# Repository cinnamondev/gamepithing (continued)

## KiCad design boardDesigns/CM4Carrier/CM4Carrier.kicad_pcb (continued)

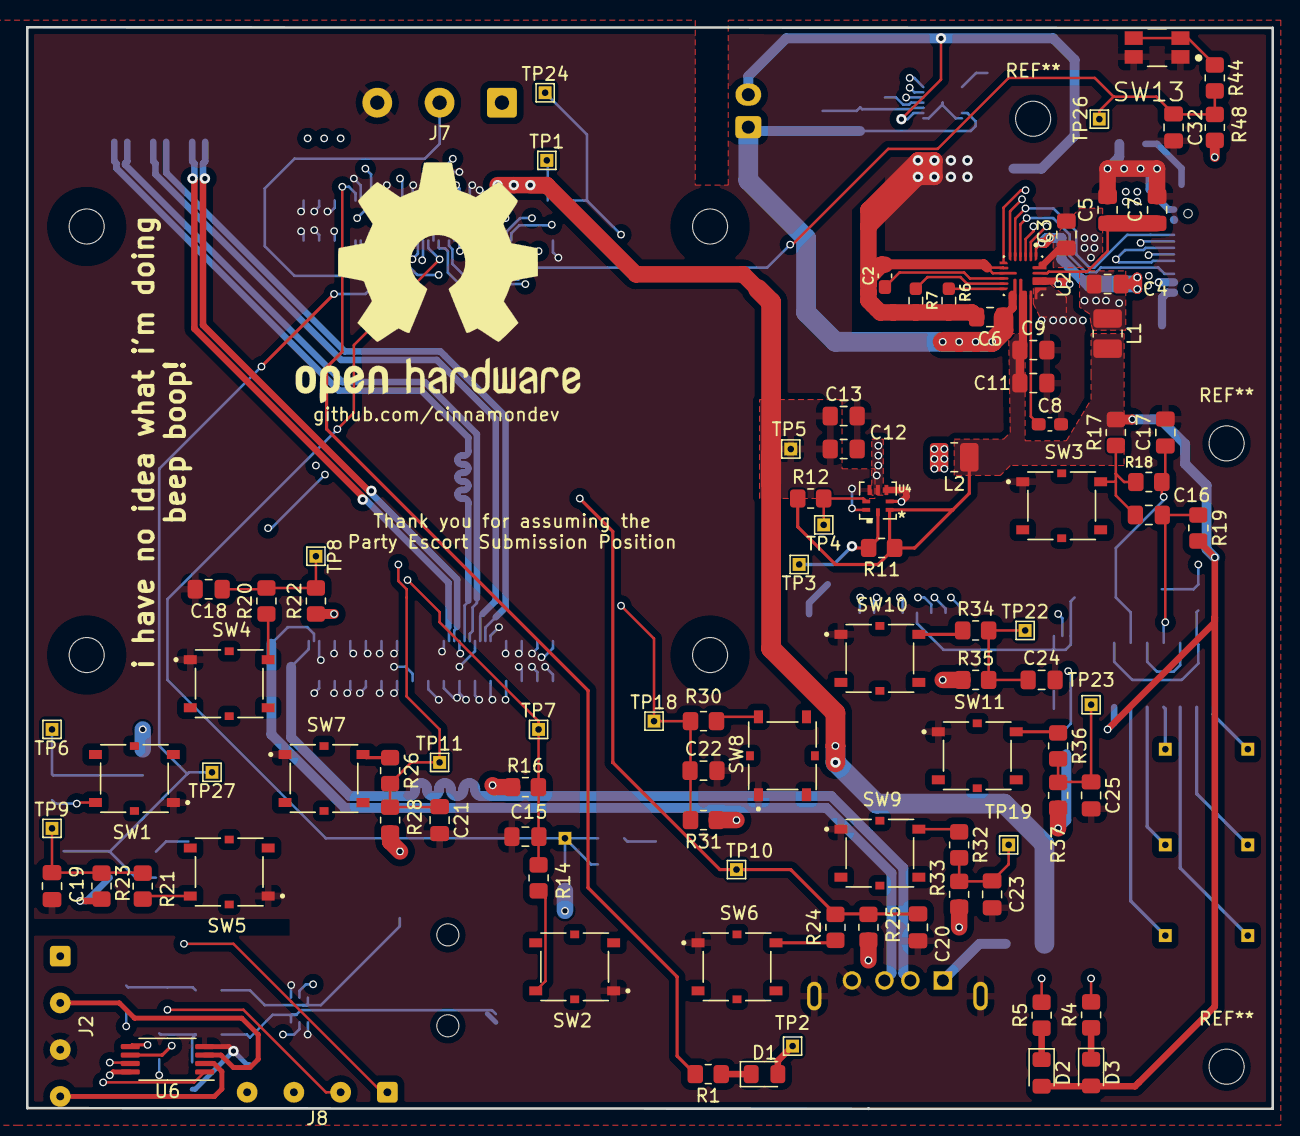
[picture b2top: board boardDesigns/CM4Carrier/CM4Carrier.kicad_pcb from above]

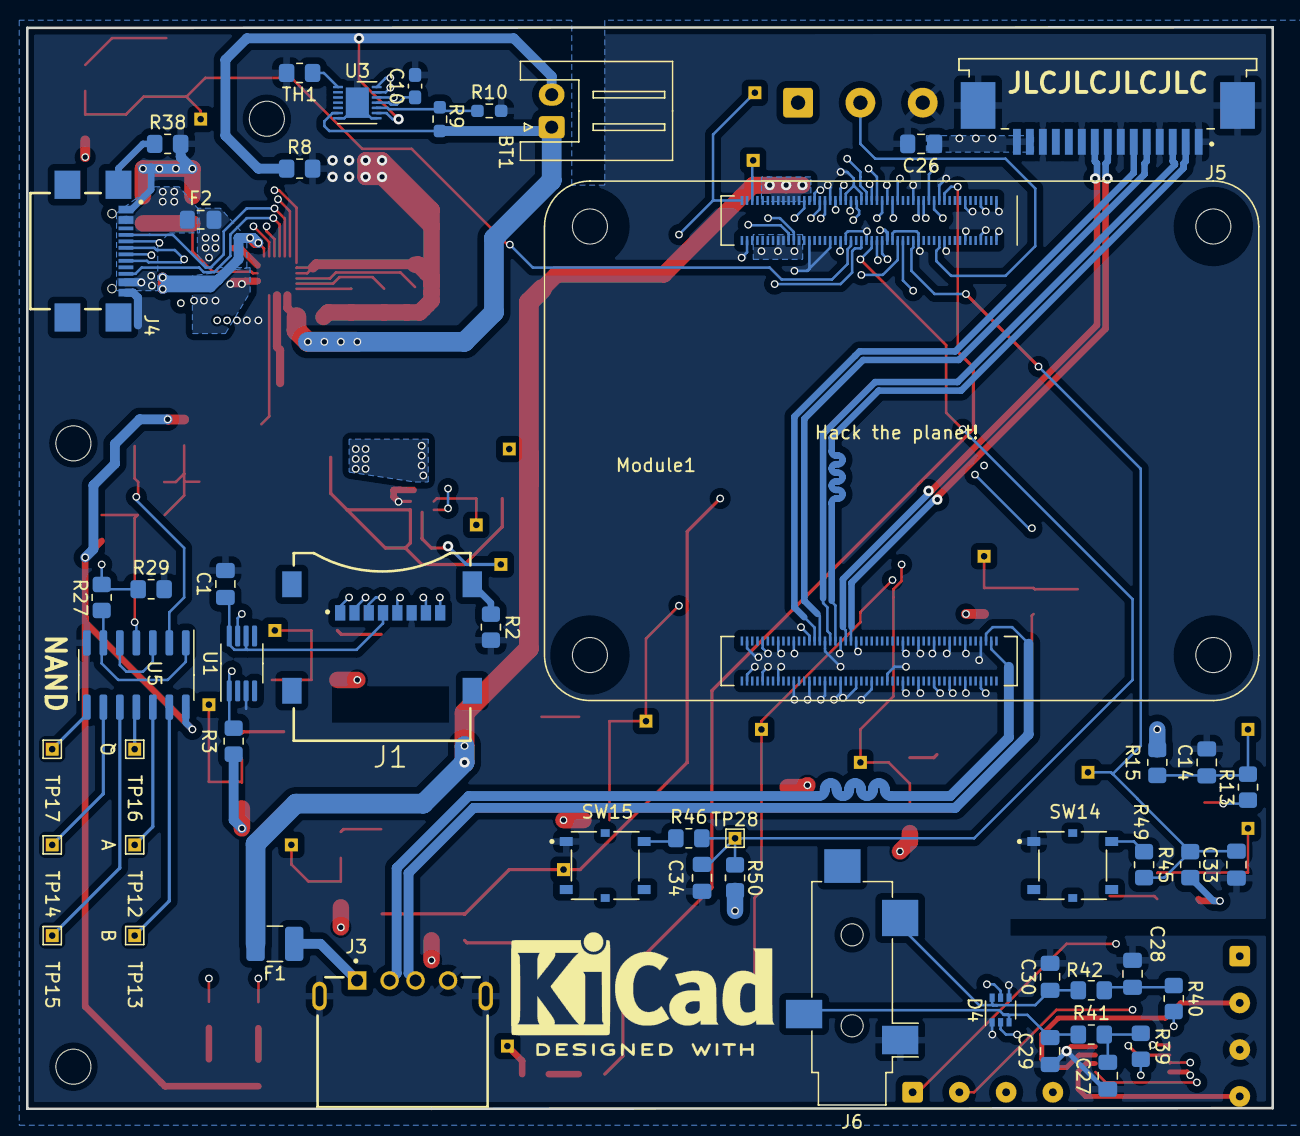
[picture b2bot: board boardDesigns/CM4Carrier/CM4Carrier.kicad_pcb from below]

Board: 4 copper layers, 95.9 x 83.3 mm, 145 parts (51 on the bottom side), 105 nets.

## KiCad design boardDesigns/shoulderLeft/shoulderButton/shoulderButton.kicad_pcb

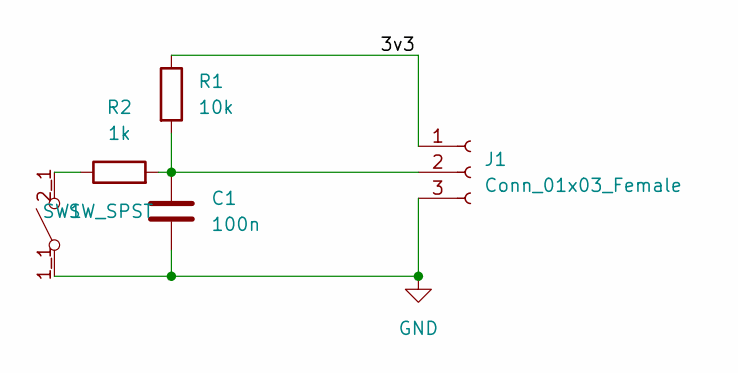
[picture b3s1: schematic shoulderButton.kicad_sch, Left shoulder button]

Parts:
C1: 100n; C_0805_2012Metric_Pad1.18x1.45mm_HandSolder
J1: Conn_01x03_Female; SolderWire-0.1sqmm_1x03_P3.6mm_D0.4mm_OD1mm
R1: 10k; R_0805_2012Metric_Pad1.20x1.40mm_HandSolder
R2: 1k; R_0805_2012Metric_Pad1.20x1.40mm_HandSolder
SW1: SW_SPST; SW_EVQ-P7J01P

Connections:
/3v3: J1.1, R1.1
GND: C1.2, J1.3, SW1.1_1 (A), SW1.1_2 (A)
unnamed: C1.1, J1.2, R1.2, R2.2
unnamed: R2.1, SW1.2_1 (B), SW1.2_2 (B)

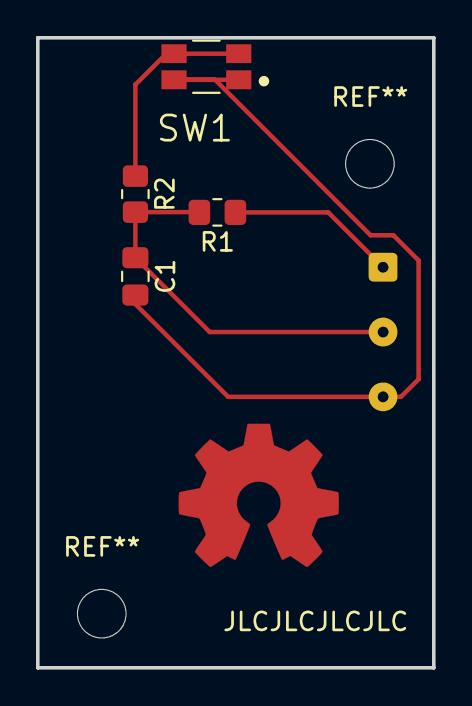
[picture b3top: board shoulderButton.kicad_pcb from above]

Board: 2 copper layers, 22.0 x 35.0 mm, 5 parts (1 on the bottom side), 4 nets.

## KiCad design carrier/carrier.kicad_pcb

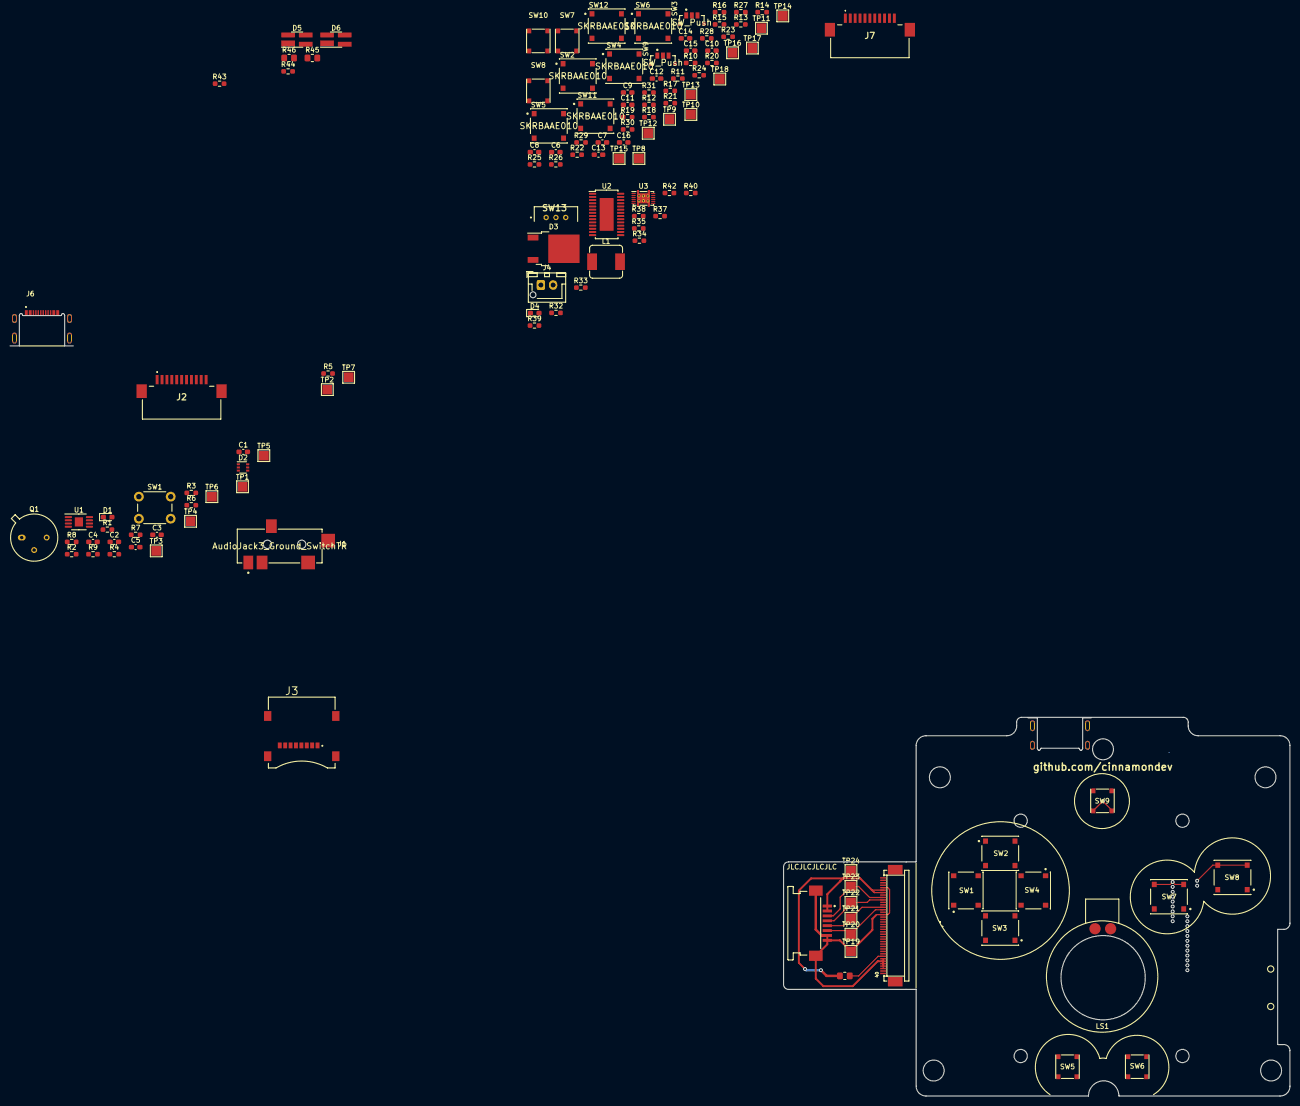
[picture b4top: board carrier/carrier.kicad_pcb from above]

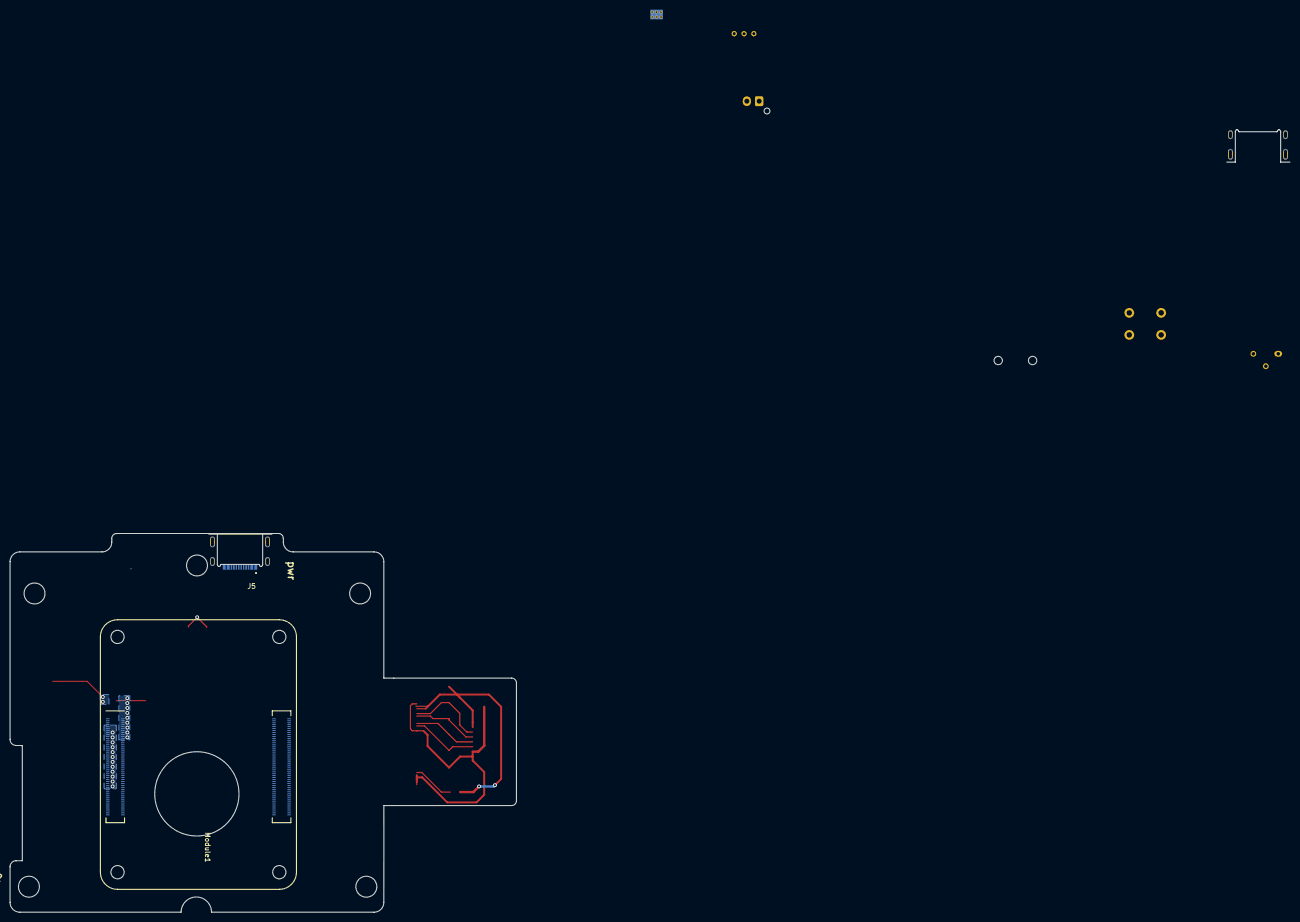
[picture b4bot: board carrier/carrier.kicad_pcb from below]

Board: 4 copper layers, 129 parts (2 on the bottom side), 87 nets.

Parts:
C1, C3: 33n; C_0603_1608Metric_Pad1.08x0.95mm_HandSolder
C2, C4: 10u; C_0603_1608Metric_Pad1.08x0.95mm_HandSolder
C5: 10uF; C_0603_1608Metric_Pad1.08x0.95mm_HandSolder
C6, C7, C8, C9, C10, C11, C12, C13, C14, C15, C16: 100n; C_0603_1608Metric_Pad1.08x0.95mm_HandSolder
D1: LED; LED_0603_1608Metric_Pad1.05x0.95mm_HandSolder
D2: BAV99S; SOT-363_SC-70-6
D3: D_Schottky; TO-252-2
D4: PG; LED_0603_1608Metric_Pad1.05x0.95mm_HandSolder
D5: 8240119; SOT-143R_Reverse_Handsoldering
D6: 8240116; SOT-143R_Reverse_Handsoldering
J1: AudioJack3_Ground_SwitchTR; CUI-SJ-43515TS-SMT-TR-0
J2, J7: Conn_01x10; 522711169
J3: Micro_SD_Card; GCT_MEM2067-02-180-00-A_REVB
J4: JST BATTERY CONN.; JST_XH_B2B-XH-AM_1x02_P2.50mm_Vertical
J5, J6#2: USB_C_Receptacle_USB2.0; GCT_USB4510-03-1-A_REVA
J6: 52271-0879; Molex-52271-0879-Manufacturer_Recommended
L1: 1uH; L_Sumida_CDMC6D28_7.25x6.5mm
LS1: Speaker; speaker
Module1: ComputeModule4-CM4; Raspberry-Pi-4-Compute-Module
Q1: 2N2219; TO-39-3
R1, R37: 220; R_0603_1608Metric_Pad0.98x0.95mm_HandSolder
R2, R34: 1M; R_0603_1608Metric_Pad0.98x0.95mm_HandSolder
R3, R5: 270; R_0603_1608Metric_Pad0.98x0.95mm_HandSolder
R4, R6: 150; R_0603_1608Metric_Pad0.98x0.95mm_HandSolder
R7: 15k; R_0603_1608Metric_Pad0.98x0.95mm_HandSolder
R8: 12k 1%; R_0603_1608Metric_Pad0.98x0.95mm_HandSolder
R9: 0; R_0603_1608Metric_Pad0.98x0.95mm_HandSolder
R10, R12, R14, R15, R18, R20, R22, R24, R26, R28, R30: 1k; R_0603_1608Metric_Pad0.98x0.95mm_HandSolder
R11, R13, R16, R17, R19, R21, R23, R25, R27, R29, R31, R39: 10k; R_0603_1608Metric_Pad0.98x0.95mm_HandSolder
R32: nc; R_0603_1608Metric_Pad0.98x0.95mm_HandSolder
R33: 540k; R_0603_1608Metric_Pad0.98x0.95mm_HandSolder
R35: 270k; R_0603_1608Metric_Pad0.98x0.95mm_HandSolder
R38, R40, R42, R43, R44: 5.1k; R_0603_1608Metric_Pad0.98x0.95mm_HandSolder
R45, R46: 56k; R_0805_2012Metric_Pad1.20x1.40mm_HandSolder
R47: 33; R_0805_2012Metric_Pad1.20x1.40mm_HandSolder
SW1, SW2, SW3#2, SW4, SW7, SW8#2: SKRRACE010; ALPS-SKRRACE010-0-0-MFG
SW1#2: SW_Push; SW_PUSH_6mm_H4.3mm
SW2#2, SW4#2, SW5, SW6, SW11, SW12: SKRBAAE010; ALPS-SKRRACE010-0-0-MFG
SW3, SW9: SW_Push; Panasonic-EVP-AEJB2A-MFG
SW5#2, SW6#2, SW9#2: SKRBAAE010
SW7#2, SW8, SW10: SKRRACE010; SKRBAAE010
SW13: SW_SPDT; SS3HVB
TP1: GLOBALEN; TestPoint_Pad_2.0x2.0mm
TP2, TP19: GND; TestPoint_Pad_2.0x2.0mm
TP3, TP20: MOSI; TestPoint_Pad_2.0x2.0mm
TP4, TP21: MISO; TestPoint_Pad_2.0x2.0mm
TP5, TP22: SCLK; TestPoint_Pad_2.0x2.0mm
TP6, TP23: CEO_N; TestPoint_Pad_2.0x2.0mm
TP7, TP24: +3.3V; TestPoint_Pad_2.0x2.0mm
TP8: LEFT; TestPoint_Pad_2.0x2.0mm
TP9: L; TestPoint_Pad_2.0x2.0mm
TP10: UP; TestPoint_Pad_2.0x2.0mm
TP11: DOWN; TestPoint_Pad_2.0x2.0mm
TP12: RIGHT; TestPoint_Pad_2.0x2.0mm
TP13: R; TestPoint_Pad_2.0x2.0mm
TP14: BKL; TestPoint_Pad_2.0x2.0mm
TP15: SEL; TestPoint_Pad_2.0x2.0mm
TP16: STR; TestPoint_Pad_2.0x2.0mm
TP17: B; TestPoint_Pad_2.0x2.0mm
TP18: A; TestPoint_Pad_2.0x2.0mm
U1: AP22814AW5; MSOP-8-1EP_3x3mm_P0.65mm_EP1.68x1.88mm
U2: MAX1709; TSSOP-28-1EP_4.4x9.7mm_P0.65mm_EP2.85x6.7mm
U3: BQ27441DRZT-G1B; Texas_S-PDSO-N12
U4: ER-CON40HT-1

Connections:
/+3.3v: D1.2 (A), D2.2 (K2), D2.5 (K4), J2.8, J2.9, J2.10, Module1.78 (GPIO_VREF(1.8v/3.3v_Input)), Module1.84 (+3.3v_(Output)), R8.1, R11.1, R13.1, R16.1, R17.1, R19.1, R21.1, R23.1, R25.1, R27.1, R29.1, R31.1, TP7.1, U1.2 (IN)
/+5v: D3.1 (K), D4.2 (A), D6.4 (VDD), LS1.1, Module1.77 (+5v_(Input)), R7.1, R35.1, R45.1, R46.1
/Battery Charger/+3.3v: R38.1, R40.1, R42.1
/Battery Charger/BAT+: J4.2, U3.6 (BAT), U3.7 (SRN)
/Battery Charger/GPOUT: R38.2, U3.12 (GPOUT)
/Battery Charger/POWERSWITCH: R33.2, R35.2, SW13.B1 (C)
/Battery Charger/SCL: R42.2, U3.2 (SCL)
/Battery Charger/SDA: R40.2, U3.1 (SDA)
/Battery Charger/VG3H: L1.2, U3.8 (SRP)
/Buttons/BTN_A: C16.1, Module1.41 (GPIO25), R30.2, R31.2, TP18.1
/Buttons/BTN_B: C15.1, Module1.29 (GPIO16), R28.2, R29.2, TP17.1
/Buttons/BTN_BACKLIGHT: C12.1, Module1.27 (GPIO20), R22.2, R23.2
/Buttons/BTN_SELECT: C11.1, Module1.45 (GPIO24), R20.2, R21.2
/Buttons/BTN_START: C14.1, Module1.25 (GPIO21), R26.2, R27.2
/Buttons/DPAD_DOWN: C9.1, Module1.34 (GPIO5), R15.2, R17.2, TP11.1
/Buttons/DPAD_LEFT: C6.1, Module1.24 (GPIO26), R10.2, R11.2, TP8.1
/Buttons/DPAD_RIGHT: C10.1, Module1.31 (GPIO12), R18.2, R19.2
/Buttons/DPAD_UP: C8.1, Module1.50 (GPIO17), R14.2, R16.2, TP10.1
/Buttons/SHOULDER_L: C7.1, Module1.46 (GPIO22), R12.2, R13.2, TP9.1
/Buttons/SHOULDER_R: C13.1, Module1.47 (GPIO23), R24.2, R25.2, TP13.1
/CM4/AUX0: Module1.49 (GPIO18), R5.1
/CM4/AUX1: Module1.26 (GPIO19), R3.1
/CM4/GLOBAL_EN: Module1.99 (Global_EN), SW1#2.1, TP1.1
/CM4/SCREEN_CE0_N: J2.7, Module1.39 (GPIO8), TP6.1
/CM4/SCREEN_MISO: J2.5, Module1.40 (GPIO9), TP4.1
/CM4/SCREEN_MOSI: J2.4, Module1.44 (GPIO10), TP3.1
/CM4/SCREEN_SCLK: J2.6, Module1.38 (GPIO11), TP5.1
/CM4/SD_CLK: J3.5 (CLK), Module1.57 (SD_CLK)
/CM4/SD_CMD: J3.3 (CMD), Module1.62 (SD_CMD)
/CM4/SD_DAT0: J3.7 (DAT0), Module1.63 (SD_DAT0)
/CM4/SD_DAT1: J3.8 (DAT1), Module1.67 (SD_DAT1)
/CM4/SD_DAT2: J3.1 (DAT2), Module1.69 (SD_DAT2)
/CM4/SD_DAT3: J3.2 (DAT3/CD), Module1.61 (SD_DAT3)
/CM4/SD_PWR: C5.1, J3.4 (VDD)
/CM4/SD_PWR_ON: Module1.75 (SD_PWR_ON), R8.2, U1.4 (EN)
/Connectors/USB2_D+: D6.2 (I/O1), J5.A6 (D+), J5.B6 (D+), Module1.105 (USB2_P)
/Connectors/USB2_D-: D6.3 (I/O2), J5.A7 (D-), J5.B7 (D-), Module1.103 (USB2_N)
/Display board (SNAP OFF BOARD)/+3.3v: J6.1, J6.2, J7.8, J7.9, J7.10, R47.1, TP24.1, U4.6 (IOVCC), U4.7 (VCI), U4.39 (IM1), U4.40 (IM2)
/Display board (SNAP OFF BOARD)/SPI0_CE0_N: J6.3, J7.7, TP23.1, U4.9 (CS/SPI_CS)
/Display board (SNAP OFF BOARD)/SPI0_MOSI: J6.6, J7.4, TP20.1, U4.14 (SDO_SPI)
/Display board (SNAP OFF BOARD)/SPI0_SCLK: J6.4, J7.6, TP22.1, U4.10 (DC/SCL_SPI)
/Display board (SNAP OFF BOARD)/SPI_MISO: J6.5, J7.5, TP21.1, U4.13 (SDI_SPI_SDA)
GND: C1.1, C3.1, C5.2, C6.2, C7.2, C8.2, C9.2, C10.2, C13.2, C15.2, C16.2, D2.1 (A1), D2.4 (A3), D5.1 (GND), D6.1 (GND), J2.1, J2.2, J2.3, J3.6 (VSS), J4.1, Module1.1 (GND), Module1.2 (GND), Module1.3 (Ethernet_Pair3_P), Module1.4 (Ethernet_Pair1_P), Module1.5 (Ethernet_Pair3_N), Module1.6 (Ethernet_Pair1_N), Module1.7 (GND), Module1.8 (GND), Module1.9 (Ethernet_Pair2_N), Module1.10 (Ethernet_Pair0_N), Module1.11 (Ethernet_Pair2_P), Module1.12 (Ethernet_Pair0_P), Module1.13 (GND), Module1.14 (GND), Module1.15 (Ethernet_nLED3(3.3v)), Module1.16 (Ethernet_SYNC_IN(1.8v)), Module1.17 (Ethernet_nLED2(3.3v)), Module1.18 (Ethernet_SYNC_OUT(1.8v)), Module1.19 (Ethernet_nLED1(3.3v)), Module1.20 (EEPROM_nWP), Module1.22 (GND), Module1.23 (GND), Module1.32 (GND), Module1.33 (GND), Module1.42 (GND), Module1.43 (GND), Module1.52 (GND), Module1.53 (GND), Module1.59 (GND), Module1.60 (GND), Module1.65 (GND), Module1.66 (GND), Module1.71 (GND), Module1.74 (GND), Module1.98 (GND), Module1.101 (USB_OTG_ID), Module1.102 (PCIe_CLK_nREQ), Module1.107 (GND), Module1.108 (GND), Module1.110 (PCIe_CLK_P), Module1.112 (PCIe_CLK_N), Module1.113 (GND), Module1.114 (GND), Module1.116 (PCIe_RX_P), Module1.118 (PCIe_RX_N), Module1.119 (GND), Module1.120 (GND), Module1.122 (PCIe_TX_P), Module1.124 (PCIe_TX_N), Module1.125 (GND), Module1.126 (GND), Module1.128 (CAM0_D0_N), Module1.130 (CAM0_D0_P), Module1.131 (GND), Module1.132 (GND), Module1.134 (CAM0_D1_N), Module1.136 (CAM0_D1_P), Module1.137 (GND), Module1.138 (GND), Module1.140 (CAM0_C_N), Module1.142 (CAM0_C_P), Module1.144 (GND), Module1.146 (HDMI1_TX2_P), Module1.147 (HDMI1_SCL), Module1.148 (HDMI1_TX2_N), Module1.150 (GND), Module1.152 (HDMI1_TX1_P), Module1.154 (HDMI1_TX1_N), Module1.155 (GND), Module1.156 (GND), Module1.157 (DSI0_D0_N), Module1.158 (HDMI1_TX0_P), Module1.159 (DSI0_D0_P), Module1.160 (HDMI1_TX0_N), Module1.161 (GND), Module1.162 (GND), Module1.163 (DSI0_D1_N), Module1.164 (HDMI1_CLK_P), Module1.165 (DSI0_D1_P), Module1.166 (HDMI1_CLK_N), Module1.167 (GND), Module1.168 (GND), Module1.169 (DSI0_C_N), Module1.171 (DSI0_C_P), Module1.173 (GND), Module1.174 (GND), Module1.175 (DSI1_D0_N), Module1.177 (DSI1_D0_P), Module1.179 (GND), Module1.180 (GND), Module1.181 (DSI1_D1_N), Module1.183 (DSI1_D1_P), Module1.185 (GND), Module1.186 (GND), Module1.187 (DSI1_C_N), Module1.189 (DSI1_C_P), Module1.191 (GND), Module1.192 (GND), Module1.193 (DSI1_D2_N), Module1.194 (DSI1_D3_N), Module1.195 (DSI1_D2_P), Module1.196 (DSI1_D3_P), Module1.197 (GND), Module1.198 (GND), Q1.1 (E), R2.2, R4.1, R6.2, R9.1, R32.2, R33.1, R34.1, R37.2, R39.2, R43.2, R44.2, SW1.2, SW1.4, SW2.2, SW2.4, SW2#2.2, SW2#2.4, SW3.1, SW3#2.2, SW3#2.4, SW4.2, SW4.4, SW4#2.2, SW4#2.4, SW5.2, SW5.4, SW5#2.2, SW5#2.4, SW6.2, SW6.4, SW6#2.2, SW6#2.4, SW7.2, SW7.4, SW7#2.2, SW8.2, SW8#2.2, SW8#2.4, SW9.1, SW9#2.2, SW9#2.4, SW10.2, SW11.2, SW11.4, SW12.2, SW12.4, SW13.C1 (B), TP2.1, U1.1 (GND), U3.3 (VSS), U3.13 (PAD)
GND1: J6.7, J6.8, J6.MP1, J6.MP2, U4.5 (GND), U4.16 (GND), U4.34 (LEDK), U4.35 (LEDK), U4.36 (LEDK), U4.37 (GND), U4.38 (IMO)
unnamed: C1.2, C2.1, R3.2, R4.2
unnamed: C2.2, D2.6 (K3A4)
unnamed: C3.2, C4.1, R5.2, R6.1
unnamed: C4.2, D2.3 (K1A2)
unnamed: C11.2, SW7#2.4
unnamed: C12.2, SW8.4
unnamed: C14.2, SW10.4
unnamed: D1.1 (K), R1.2
unnamed: D3.2 (A), L1.1
unnamed: D4.1 (K), R37.1
unnamed: D5.2 (I/O1), J6#2.A6 (D+), J6#2.B6 (D+)
unnamed: D5.3 (I/O2), J6#2.A7 (D-), J6#2.B7 (D-)
unnamed: Q1.2 (B), R7.2
unnamed: J3.9 (SHIELD), R9.2
unnamed: J5.A5 (CC1), R46.2
unnamed: J5.B5 (CC2), R45.2
unnamed: J6#2.A5 (CC1), R44.1
unnamed: J6#2.B5 (CC2), R43.1
unnamed: J7.1, J7.2, J7.3, TP19.1
unnamed: LS1.2, Q1.3 (C)
unnamed: Module1.21 (PI_nLED_Activity), R1.1
unnamed: Module1.85 (+5v_(Input)), Module1.87 (+5v_(Input))
unnamed: SW1.1, SW1.3
unnamed: R2.1, SW1#2.2
unnamed: SW2.1, SW2.3
unnamed: SW3#2.1, SW3#2.3
unnamed: SW4.1, SW4.3
unnamed: SW8#2.1, SW8#2.3
unnamed: R10.1, SW2#2.1, SW2#2.3
unnamed: SW7.1, SW7.3
unnamed: R12.1, SW3.2
unnamed: R14.1, SW4#2.1, SW4#2.3
unnamed: R15.1, SW5.1, SW5.3
unnamed: R18.1, SW6.1, SW6.3
unnamed: R20.1, SW7#2.3
unnamed: R22.1, SW8.3
unnamed: R24.1, SW9.2
unnamed: R26.1, SW5#2.1, SW5#2.3, SW10.3
unnamed: R28.1, SW9#2.1, SW9#2.3, SW11.1, SW11.3
unnamed: R30.1, SW12.1, SW12.3
unnamed: SW6#2.1, SW6#2.3
unnamed: R39.1, U3.10 (BIN)
unnamed: R47.2, U4.33 (LEDA)

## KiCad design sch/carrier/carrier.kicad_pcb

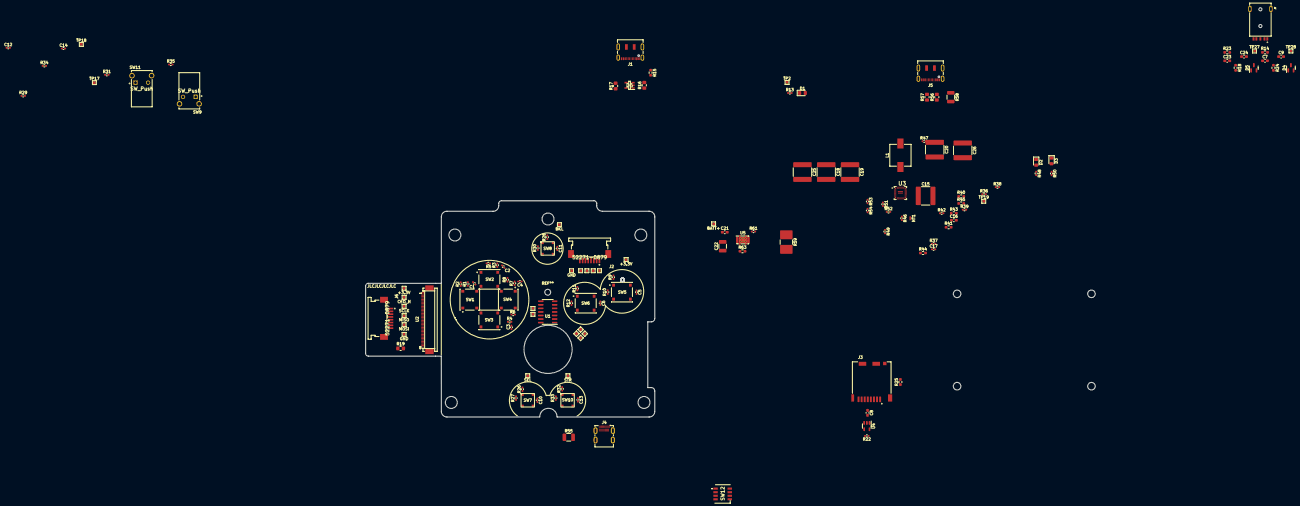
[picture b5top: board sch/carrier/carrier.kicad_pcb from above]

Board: 2 copper layers, 103.3 x 77.2 mm, 146 parts (1 on the bottom side), 110 nets, no tracks yet.

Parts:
C1, C2, C3, C4, C5, C6, C10, C11, C12, C13, C14: 0.1uF; C_0402_1005Metric_Pad0.74x0.62mm_HandSolder
C7, C23: 33n; C_0603_1608Metric_Pad1.08x0.95mm_HandSolder
C8: 10uF; C_0603_1608Metric_Pad1.08x0.95mm_HandSolder
C9, C24: 10u; C_0603_1608Metric_Pad1.08x0.95mm_HandSolder
C15: 10uF; C_2225_5664Metric_Pad1.80x6.60mm_HandSolder
C16: 100nF; C_0603_1608Metric_Pad1.08x0.95mm_HandSolder
C17: 100nf; C_0402_1005Metric_Pad0.74x0.62mm_HandSolder
C18: 22u; C_2225_5664Metric_Pad1.80x6.60mm_HandSolder
C19, C20, C25, C26: 10u; C_2225_5664Metric_Pad1.80x6.60mm_HandSolder
C21: 1uF; C_0603_1608Metric_Pad1.08x0.95mm_HandSolder
C22: 0.47uF; C_1210_3225Metric_Pad1.33x2.70mm_HandSolder
D1, D2, D3: LED; LED_0805_2012Metric_Pad1.15x1.40mm_HandSolder
D4, D5: BAV99; SOT-23
D6: 824011; SOT95P280X145-5N
J1, J5: USB_C_Receptacle_USB2.0; USB_C_Receptacle_JAE_DX07S016JA1R1500
J2, J6: 52271-0879; Molex-52271-0879-Manufacturer_Recommended
J3: Micro_SD_Card; HRS_DM3CS-SF
J4: HDMI_D_1.4; HDMI_Micro-D_Molex_46765-1x01
J7: AudioJack3_Switch; audio
L1: 6.8uH; L_Wuerth_WE-PD-Typ-M-Typ-S_Handsoldering
Module0: ComputeModule4-CM4; Raspberry-Pi-4-Compute-Module
NT1: NetTie; NetTie-2_SMD_Pad0.5mm
R1, R3, R4, R7, R9, R11, R26, R28, R29, R32, R34, R36, R39: 1k; R_0402_1005Metric_Pad0.72x0.64mm_HandSolder
R2, R5, R6, R8, R10, R12, R27, R30, R31, R33, R35, R61: 10k; R_0402_1005Metric_Pad0.72x0.64mm_HandSolder
R13: 220; R_0402_1005Metric_Pad0.72x0.64mm_HandSolder
R14, R23: 270; R_0603_1608Metric_Pad0.98x0.95mm_HandSolder
R15, R25: 0; R_0603_1608Metric_Pad0.98x0.95mm_HandSolder
R16, R17: 56k; R_0805_2012Metric_Pad1.20x1.40mm_HandSolder
R18, R24: 150; R_0603_1608Metric_Pad0.98x0.95mm_HandSolder
R19: 33; R_0805_2012Metric_Pad1.20x1.40mm_HandSolder
R22: 12k 1%; R_0402_1005Metric_Pad0.72x0.64mm_HandSolder
R37: 9k; R_0402_1005Metric_Pad0.72x0.64mm_HandSolder
R38: 1.3k; R_0402_1005Metric_Pad0.72x0.64mm_HandSolder
R40, R41: 10.5k; R_0603_1608Metric_Pad0.98x0.95mm_HandSolder
R42: 16k; R_0402_1005Metric_Pad0.72x0.64mm_HandSolder
R43, R63: 10k; R_0603_1608Metric_Pad0.98x0.95mm_HandSolder
R44: 3k; R_0603_1608Metric_Pad0.98x0.95mm_HandSolder
R45: 55.2k; R_0603_1608Metric_Pad0.98x0.95mm_HandSolder
R46: 120k; R_0402_1005Metric_Pad0.72x0.64mm_HandSolder
R47: 20m; R_0402_1005Metric_Pad0.72x0.64mm_HandSolder
R48, R49, R50: 2.49k; R_0402_1005Metric_Pad0.72x0.64mm_HandSolder
R51, R52, R53, R54: 10.5k; R_0402_1005Metric_Pad0.72x0.64mm_HandSolder
R55, R58: 0; R_1210_3225Metric_Pad1.30x2.65mm_HandSolder
R56, R57: 5.1k; R_0805_2012Metric_Pad1.20x1.40mm_HandSolder
R59: 10m; R_2816_7142Metric_Pad3.20x4.45mm_HandSolder
SW1, SW2, SW3, SW4, SW5, SW6: SKRRACE010; ALPS-SKRRACE010-0-0-MFG
SW7, SW8, SW10: SKRBAAE010
SW9, SW11: SW_Push; TE_Connectivity-1-1825027-1-0-0-Recommended_Land_Pattern_
SW12: SW_DIP_x04; CHS04TA1
TP1, TP20: GND; TestPoint_Pad_1.0x1.0mm
TP2: Activity; TestPoint_Pad_1.0x1.0mm
TP3, TP21: CEO_N; TestPoint_Pad_1.0x1.0mm
TP4, TP22: SCLK; TestPoint_Pad_1.0x1.0mm
TP5, TP23: MISO; TestPoint_Pad_1.0x1.0mm
TP6: UP; TestPoint_Pad_1.0x1.0mm
TP7: DOWN; TestPoint_Pad_1.0x1.0mm
TP8: LEFT; TestPoint_Pad_1.0x1.0mm
TP9: RIGHT; TestPoint_Pad_1.0x1.0mm
TP10: A; TestPoint_Pad_1.0x1.0mm
TP11: B; TestPoint_Pad_1.0x1.0mm
TP12, TP24: MOSI; TestPoint_Pad_1.0x1.0mm
TP13, TP25: +3.3V; TestPoint_Pad_1.0x1.0mm
TP14: BKL; TestPoint_Pad_1.0x1.0mm
TP15: SEL; TestPoint_Pad_1.0x1.0mm
TP16: STR; TestPoint_Pad_1.0x1.0mm
TP17: L; TestPoint_Pad_1.0x1.0mm
TP18: R; TestPoint_Pad_1.0x1.0mm
TP19: +5v Output; TestPoint_Pad_1.0x1.0mm
TP26: BATT+; TestPoint_Pad_1.0x1.0mm
TP27: AUXR; TestPoint_Pad_1.0x1.0mm
TP28: AUXL; TestPoint_Pad_1.0x1.0mm
U1: SN74HC14N; SO-14_3.9x8.65mm_P1.27mm
U2: ER-CON40HT-1
U3: MP2636GR-P; IC_MP2636GR-P
U4: AP22814AW5; SOT-23-5
U5: BQ27441DRZR-G1B; Texas_S-PDSO-N12

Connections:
/+3.3v: D1.2 (A), D4.2 (A), D5.2 (A), J2.1, J2.2, Module0.78 (GPIO_VREF(1.8v/3.3v_Input)), Module0.84 (+3.3v_(Output)), R2.1, R5.1, R6.1, R8.1, R10.1, R12.1, R22.1, R27.1, R30.1, R31.1, R33.1, R35.1, TP13.1, U1.14 (VCC), U4.5 (IN)
/+5v: C18.1, C19.1, C25.1, D6.5 (VDD), J1.A4 (VBUS), J1.A9 (VBUS), J1.B4 (VBUS), J1.B9 (VBUS), J4.19 (+5V), Module0.77 (+5v_(Input)), Module0.79 (+5v_(Input)), Module0.81 (+5v_(Input)), Module0.83 (+5v_(Input)), Module0.85 (+5v_(Input)), Module0.87 (+5v_(Input)), R16.1, R17.1, R43.2, R53.1, U3.3 (SYS), U3.20 (SYS), U3.29 (SYS)
/Battery Charger/BATT: C20.1, C26.1, R47.2, R59.2, U3.17 (BATT), U5.7 (SRN)
/Battery Charger/CHRG: C15.1, J5.A4 (VBUS), J5.A9 (VBUS), J5.B4 (VBUS), J5.B9 (VBUS), R36.1, R38.1, U3.4 (VIN), U3.19 (VIN), U3.30 (VIN)
/Battery Charger/_CHIP_VCC: C16.2, R40.1, R41.1, R51.1, U3.5 (VCC)
/Battery/FUEL_SCL: Module0.80 (SCL0), U5.2 (SCL)
/Battery/FUEL_SDA: Module0.82 (SDA0), U5.1 (SDA)
/Buttons/BTN_A: Module0.41 (GPIO25), TP10.1, U1.10 (5Y)
/Buttons/BTN_B: Module0.29 (GPIO16), TP11.1, U1.12 (6Y)
/Buttons/BTN_BACKLIGHT: C11.1, Module0.27 (GPIO20), R28.2, R30.2, TP14.1
/Buttons/DPAD_DOWN: Module0.55 (GPIO14), TP7.1, U1.6 (3Y)
/Buttons/DPAD_LEFT: Module0.28 (GPIO13), TP8.1, U1.8 (4Y)
/Buttons/DPAD_RIGHT: Module0.31 (GPIO12), TP9.1, U1.4 (2Y)
/Buttons/DPAD_UP: Module0.50 (GPIO17), TP6.1, U1.2 (1Y)
/Buttons/GLOBAL_EN: Module0.99 (Global_EN), SW12.1
/Buttons/SELECT: C10.1, Module0.25 (GPIO21), R26.2, R27.2, TP15.1
/Buttons/SHOULDER_L: C12.1, Module0.46 (GPIO22), R29.2, R31.2, TP17.1
/Buttons/SHOULDER_R: C14.1, Module0.47 (GPIO23), R34.2, R35.2, TP18.1
/Buttons/START: C13.1, Module0.45 (GPIO24), R32.2, R33.2, TP16.1
/Buttons/__B_A: C5.1, R9.2, R10.2, U1.11 (5A)
/Buttons/__B_B: C6.1, R11.2, R12.2, U1.13 (6A)
/Buttons/__DP_D: C3.1, R4.2, R6.2, U1.5 (3A)
/Buttons/__DP_L: C1.2, R1.2, R2.2, U1.9 (4A)
/Buttons/__DP_R: C4.1, R7.2, R8.2, U1.3 (2A)
/Buttons/__DP_U: C2.1, R3.2, R5.2, U1.1 (1A)
/CM4/AUX0: Module0.49 (GPIO18), R23.1
/CM4/AUX1: Module0.26 (GPIO19), R14.1
/CM4/SCREEN_CE0_N: J2.3, Module0.39 (GPIO8), TP3.1
/CM4/SCREEN_MISO: J2.5, Module0.40 (GPIO9), TP5.1
/CM4/SCREEN_MOSI: J2.6, Module0.44 (GPIO10), TP12.1
/CM4/SCREEN_SCLK: J2.4, Module0.38 (GPIO11), TP4.1
/CM4/SD_CLK: J3.5 (CLK), Module0.57 (SD_CLK)
/CM4/SD_CMD: J3.3 (CMD), Module0.62 (SD_CMD)
/CM4/SD_DAT0: J3.7 (DAT0), Module0.63 (SD_DAT0)
/CM4/SD_DAT1: J3.8 (DAT1), Module0.67 (SD_DAT1)
/CM4/SD_DAT2: J3.1 (DAT2), Module0.69 (SD_DAT2)
/CM4/SD_DAT3: J3.2 (DAT3/CD), Module0.61 (SD_DAT3)
/CM4/SD_PWR: C8.1, J3.4 (VDD), U4.1 (OUT)
/CM4/SD_PWR_ON: Module0.75 (SD_PWR_ON), R22.2, U4.4 (EN)
/Connectors/CLK_N: J4.14 (CK-), Module0.190 (HDMI0_CLK_N)
/Connectors/CLK_P: J4.12 (CK+), Module0.188 (HDMI0_CLK_P)
/Connectors/HDMI_CEC: J4.15 (CEC), Module0.151 (HDMI0_CEC)
/Connectors/HDMI_HP: J4.1 (HPD/HEAC-), Module0.153 (HDMI0_HOTPLUG)
/Connectors/HDMI_SCL: J4.17 (SCL), Module0.200 (HDMI0_SCL)
/Connectors/HDMI_SDA: J4.18 (SDA), Module0.199 (HDMI0_SDA)
/Connectors/TX0_N: J4.11 (D0-), Module0.184 (HDMI0_TX0_N)
/Connectors/TX0_P: J4.9 (D0+), Module0.182 (HDMI0_TX0_P)
/Connectors/TX1_N: J4.8 (D1-), Module0.178 (HDMI0_TX1_N)
/Connectors/TX1_P: J4.6 (D1+), Module0.176 (HDMI0_TX1_P)
/Connectors/TX2_N: J4.5 (D2-), Module0.172 (HDMI0_TX2_N)
/Connectors/TX2_P: J4.3 (D2+), Module0.170 (HDMI0_TX2_P)
/Connectors/USB2_D+: D6.3 (I/O1), J1.A6 (D+), J1.B6 (D+), Module0.105 (USB2_P)
/Connectors/USB2_D-: D6.4 (I/O2), J1.A7 (D-), J1.B7 (D-), Module0.103 (USB2_N)
/Display board (SNAP OFF BOARD)/+3.3v: J6.1, J6.2, R19.1, TP25.1, U2.6 (IOVCC), U2.7 (VCI), U2.39 (IM1), U2.40 (IM2)
/Display board (SNAP OFF BOARD)/SPI0_CE0_N: J6.3, TP21.1, U2.9 (CS/SPI_CS)
/Display board (SNAP OFF BOARD)/SPI0_MOSI: J6.6, TP24.1, U2.14 (SDO_SPI)
/Display board (SNAP OFF BOARD)/SPI0_SCLK: J6.4, TP22.1, U2.10 (DC/SCL_SPI)
/Display board (SNAP OFF BOARD)/SPI_MISO: J6.5, TP23.1, U2.13 (SDI_SPI_SDA)
GND: C1.1, C2.2, C3.2, C4.2, C5.2, C6.2, C7.1, C8.2, C10.2, C11.2, C12.2, C13.2, C14.2, C15.2, C16.1, C17.2, C18.2, C19.2, C20.2, C21.2, C22.2, C23.1, C25.2, C26.2, D4.1 (K), D5.1 (K), D6.2 (GND), J1.A1 (GND), J1.A12 (GND), J1.B1 (GND), J1.B12 (GND), J2.7, J2.8, J2.MP1, J2.MP2, J3.6 (VSS), J4.4 (D2S), J4.7 (D1S), J4.10 (D0S), J4.13 (CKS), J4.16 (GND), J5.A1 (GND), J5.A12 (GND), J5.B1 (GND), J5.B12 (GND), J7.T, Module0.1 (GND), Module0.2 (GND), Module0.3 (Ethernet_Pair3_P), Module0.4 (Ethernet_Pair1_P), Module0.5 (Ethernet_Pair3_N), Module0.6 (Ethernet_Pair1_N), Module0.7 (GND), Module0.8 (GND), Module0.9 (Ethernet_Pair2_N), Module0.10 (Ethernet_Pair0_N), Module0.11 (Ethernet_Pair2_P), Module0.12 (Ethernet_Pair0_P), Module0.13 (GND), Module0.14 (GND), Module0.15 (Ethernet_nLED3(3.3v)), Module0.16 (Ethernet_SYNC_IN(1.8v)), Module0.17 (Ethernet_nLED2(3.3v)), Module0.18 (Ethernet_SYNC_OUT(1.8v)), Module0.19 (Ethernet_nLED1(3.3v)), Module0.20 (EEPROM_nWP), Module0.22 (GND), Module0.23 (GND), Module0.32 (GND), Module0.33 (GND), Module0.42 (GND), Module0.43 (GND), Module0.52 (GND), Module0.53 (GND), Module0.59 (GND), Module0.60 (GND), Module0.65 (GND), Module0.66 (GND), Module0.71 (GND), Module0.74 (GND), Module0.98 (GND), Module0.101 (USB_OTG_ID), Module0.102 (PCIe_CLK_nREQ), Module0.107 (GND), Module0.108 (GND), Module0.110 (PCIe_CLK_P), Module0.112 (PCIe_CLK_N), Module0.113 (GND), Module0.114 (GND), Module0.116 (PCIe_RX_P), Module0.118 (PCIe_RX_N), Module0.119 (GND), Module0.120 (GND), Module0.122 (PCIe_TX_P), Module0.124 (PCIe_TX_N), Module0.125 (GND), Module0.126 (GND), Module0.128 (CAM0_D0_N), Module0.130 (CAM0_D0_P), Module0.131 (GND), Module0.132 (GND), Module0.134 (CAM0_D1_N), Module0.136 (CAM0_D1_P), Module0.137 (GND), Module0.138 (GND), Module0.140 (CAM0_C_N), Module0.142 (CAM0_C_P), Module0.144 (GND), Module0.146 (HDMI1_TX2_P), Module0.147 (HDMI1_SCL), Module0.148 (HDMI1_TX2_N), Module0.150 (GND), Module0.152 (HDMI1_TX1_P), Module0.154 (HDMI1_TX1_N), Module0.155 (GND), Module0.156 (GND), Module0.157 (DSI0_D0_N), Module0.158 (HDMI1_TX0_P), Module0.159 (DSI0_D0_P), Module0.160 (HDMI1_TX0_N), Module0.161 (GND), Module0.162 (GND), Module0.163 (DSI0_D1_N), Module0.164 (HDMI1_CLK_P), Module0.165 (DSI0_D1_P), Module0.166 (HDMI1_CLK_N), Module0.167 (GND), Module0.168 (GND), Module0.169 (DSI0_C_N), Module0.171 (DSI0_C_P), Module0.173 (GND), Module0.174 (GND), Module0.175 (DSI1_D0_N), Module0.177 (DSI1_D0_P), Module0.179 (GND), Module0.180 (GND), Module0.181 (DSI1_D1_N), Module0.183 (DSI1_D1_P), Module0.185 (GND), Module0.186 (GND), Module0.187 (DSI1_C_N), Module0.189 (DSI1_C_P), Module0.191 (GND), Module0.192 (GND), Module0.193 (DSI1_D2_N), Module0.194 (DSI1_D3_N), Module0.195 (DSI1_D2_P), Module0.196 (DSI1_D3_P), Module0.197 (GND), Module0.198 (GND), NT1.2, R15.2, R18.2, R24.2, R25.1, R44.2, R45.2, R46.2, R48.2, R49.2, R50.2, R55.2, R56.1, R57.1, R58.2, R61.1, SW1.2, SW1.4, SW2.2, SW2.4, SW3.2, SW3.4, SW4.2, SW4.4, SW5.2, SW5.4, SW6.2, SW6.4, SW7.2, SW7.4, SW8.2, SW8.4, SW9.1, SW10.2, SW10.4, SW11.1, SW12.8, TP1.1, U1.7 (GND), U3.26 (FREQ), U3.27 (PGND), U3.28 (PGND), U4.2 (GND), U5.3 (VSS), U5.13 (PAD)
GND1: J6.7, J6.8, J6.MP1, J6.MP2, TP20.1, U2.5 (GND), U2.16 (GND), U2.34 (LEDK), U2.35 (LEDK), U2.36 (LEDK), U2.37 (GND), U2.38 (IMO)
GNDA: NT1.1, R37.2, R39.2, R42.2, R52.2, R54.2, U3.15 (AGND), U3.15_1 (AGND)
unnamed: C7.2, C9.1, R14.2, R18.1
unnamed: C9.2, D4.3 (K), J7.S, TP28.1
unnamed: C17.1, U3.8 (TMR), U3.8_1 (TMR)
unnamed: C21.1, R59.1, TP26.1, U5.6 (BAT), U5.8 (SRP)
unnamed: C22.1, R63.1, U5.5 (VDD)
unnamed: C23.2, C24.1, R23.2, R24.1
unnamed: C24.2, D5.3 (K), J7.R, TP27.1
unnamed: D1.1 (K), R13.2, TP2.1
unnamed: D2.1 (K), U3.22 (~BOOST), U3.22_1 (~BOOST)
unnamed: D2.2 (A), R48.1
unnamed: D3.1 (K), U3.23 (~CHG)
unnamed: D3.2 (A), R50.1
unnamed: J1.A5 (CC1), R16.2
unnamed: J1.B5 (CC2), R17.2
unnamed: J1.S1 (SHIELD), R15.1
unnamed: J3.9 (SHIELD), R25.2
unnamed: J4.SH, R55.1
unnamed: J5.A5 (CC1), R56.2
unnamed: J5.A6 (D+), J5.A7 (D-), J5.B6 (D+), J5.B7 (D-)
unnamed: J5.B5 (CC2), R57.2
unnamed: J5.S1 (SHIELD), R58.1
unnamed: L1.1, U3.2 (SW), U3.21 (SW)
unnamed: L1.2, R47.1, U3.18 (CSP)
unnamed: Module0.21 (PI_nLED_Activity), R13.1
unnamed: R1.1, SW1.1, SW1.3
unnamed: R3.1, SW2.1, SW2.3
unnamed: R4.1, SW3.1, SW3.3
unnamed: R7.1, SW4.1, SW4.3
unnamed: R9.1, SW5.1, SW5.3
unnamed: R11.1, SW6.1, SW6.3
unnamed: R19.2, U2.33 (LEDA)
unnamed: R26.1, SW7.1, SW7.3
unnamed: R28.1, SW8.1, SW8.3
unnamed: R29.1, SW9.2
unnamed: R32.1, SW10.1, SW10.3
unnamed: R34.1, SW11.2
unnamed: R36.2, R37.1, U3.7 (PWIN)
unnamed: R38.2, R39.1, U3.9 (REG)
unnamed: R40.2, U3.25 (EN)
unnamed: R41.2, U3.24 (MODE)
unnamed: R42.1, U3.6 (ILIM)
unnamed: R43.1, R44.1, U3.11 (FB)
unnamed: R45.1, U3.14 (OLIM)
unnamed: R46.1, U3.13 (ISET)
unnamed: R49.1, U3.10 (~ACOK)
unnamed: R51.2, R52.1, U3.16 (VB)
unnamed: R53.2, R54.1, U3.12 (NTC)
unnamed: R61.2, U5.10 (BIN)
unnamed: R63.2, U5.12 (GPOUT)

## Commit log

2021-07-02 update license to CERN-OHL-S and notes
2021-07-02 lets see if this worked
2021-07-02 FIXED LINKS
2021-07-05 push some stuff
    it sorta needs organising more though...
2021-07-08 noice.
2021-07-08 AASKHUQAWFHIU
2021-07-08 goodnight
2021-07-08 hhhhhhhhhhhhhhhhh
2021-07-08 update readme and add some text for the sheets.
2021-07-09 put some stuff on the pcb - it is going to kill me trying to get all on
2021-07-10 holy shit i hate chargers
2021-07-13 bring in line with the datasheet
2021-07-13 holy shit learning
2021-07-15 push
2021-07-15 hgfhgfhfhgfhgfhgf
2021-07-18 oh yeah
2021-07-18 azsads
2021-07-24 still alive :)
2021-07-25 get git committed
2021-07-25 aaaaaaaaaaaaaaaa
2021-07-25 changes and carrier backups
2021-07-25 gitignore fix
2021-07-26 add speaker and charger
2021-07-28 push updates
2021-07-29 adsasdas
2021-07-30 git pushed
2021-07-30 we're abt ready to do pcb i hope!
2021-07-30 aaaaaaaaaaaaaa
2021-07-30 ersfdxcv
2021-08-01 footprint assignmnt
2021-08-02 randomtexttofillthecommittext
2021-08-03 aaaaaaaaaaaaaaaaaaaaaaaaaaaaaaaa
2021-08-03 pcb time?
2021-08-03 enough for now
2021-08-06 revise board
2021-08-08 aaaaaaaaaaaaaaaaaaaaaaaaa
2021-08-08 some clean up
2021-08-08 pcb!?
2021-08-11 aaaa
2021-08-13 aaaaaa
2021-08-26 aaaaaaaaaaaaaaaaaaaaaaaaaaaaaaaaaaaaaaaaaaaaaaaaaaaaaaaaaaaaaaaaa
2021-08-27 aaaaadsa
2021-09-05 jjjjj
2021-09-27 getting back into the swing of this
    aded some stuff for the resistors, moved some stuff about, removed the schmitt inverter (software is the solution for all our problems, forever)
2021-09-29 we are nearing completion for this version
    maybe one day we will make a second version
2021-10-03 getting there!!
2021-10-31 Auto stash before merge of "master" and "origin/master"
2021-11-02 add correct charge chip
2021-11-20 thingy
2021-11-20 fixed switching and added fuel gague
2021-11-20 gitignore
2021-11-20 Clean up
2021-11-20 need to finish footprint assignments then can do rev2 pcb (cooler one)
2021-11-21 new footprints - order stuff soon
2021-11-21 buggy
2021-11-22 go back to tomrw
2021-12-17 thing
2021-12-23 chrgere
2022-03-04 symb.
2022-03-05 Adaptor board
2022-03-05 adaptor + some design wrork
2022-03-31 kjkl
2022-04-03 Additions
    - Fixed gitignore (Backups)
    - Work on buttons
    - Work on ADC for JOYSTICK
    - Work on some other stuff
2022-04-03 wiring some stuff
2022-04-03 footprints + values
    need to do some 3d babeeeeeeeeee
2022-04-06 pcb next :sunglasses:
2022-04-07 pcb babeee les goooo
2022-04-15 pcb w proper design
2022-04-15 PCB work
    Home-stretch! Remaining things:
    - Forgot Headphone jack / audio in design - add.
    - route power supply (aaaaa)
2022-04-16 LAYOUT DONE!!
    :)
2022-04-17 some fixes
    cross reference with casing
2022-04-22 fuseeeeeeeeeeeeeeeeeeeeeeeeeeeeeeeeeeeeeeeeeee
2022-04-24 add buttons
    need to adjust 3d model for buttons and add them to pcb... forgot about these.
2022-04-27 nearly done
    i do not want to do the fiddly ones
2022-05-01 routing
2022-05-01 cut up board
    need to add the button addonboard
2022-05-01 model & add break off board tommorow
2022-05-08 board outline
2022-05-08 clean up and added partly shoulder board...
2022-05-14 rev1
2022-05-14 shoulder button
2022-05-15 update ouptut
2022-06-01 differential impedence
2022-06-24 fusion export
2022-07-07 some fixes....
    small details, should not affect assembly
2022-10-21 readme update
2022-11-19 project wipe and license updating
    namely bringing in line with other projects
2023-03-09 unfinished notice
